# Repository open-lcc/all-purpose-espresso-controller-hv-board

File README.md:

# All-Purpose Espresso Controller HV Board

*Note: The HV does stand for high voltage. It's not high voltage in the technical (>1000 V) sense, but compared to the 12 V in the regular All-Purpose Espresso Controller board, 100-240 VAC is high*

This board is a companion board to the [All Purpose Espresso Controller](https://github.com/open-lcc/all-purpose-espresso-controller) board. Its purpose is to handle some common 100-240 VAC tasks, specifically it has a 12V PSU and four relays.

## Project status

The current hardware revision is R0B. That revision hasn't been manufactured yet, and while this board is pretty simple, and doesn't have any SMD soldering, you probably shouldn't be the first one to manufacture it.

## Disclaimer

Anything you do with this, you do at your own risk. This hardware hasn't even been manufactured by it's creator yet. Your machine uses both line voltage power, high pressured hot water, steam and other dangerous components. You *really* shouldn't be using this yet; in fact, you shouldn't even consider it. Risks include but are not limited to, damaging your machine, personal injury, property damage and summoning dead Cthulhu from his sleep at R'lyeh.

Also, the very purpose of this board is to do things with line voltage. The risk of injury or damage is very real.

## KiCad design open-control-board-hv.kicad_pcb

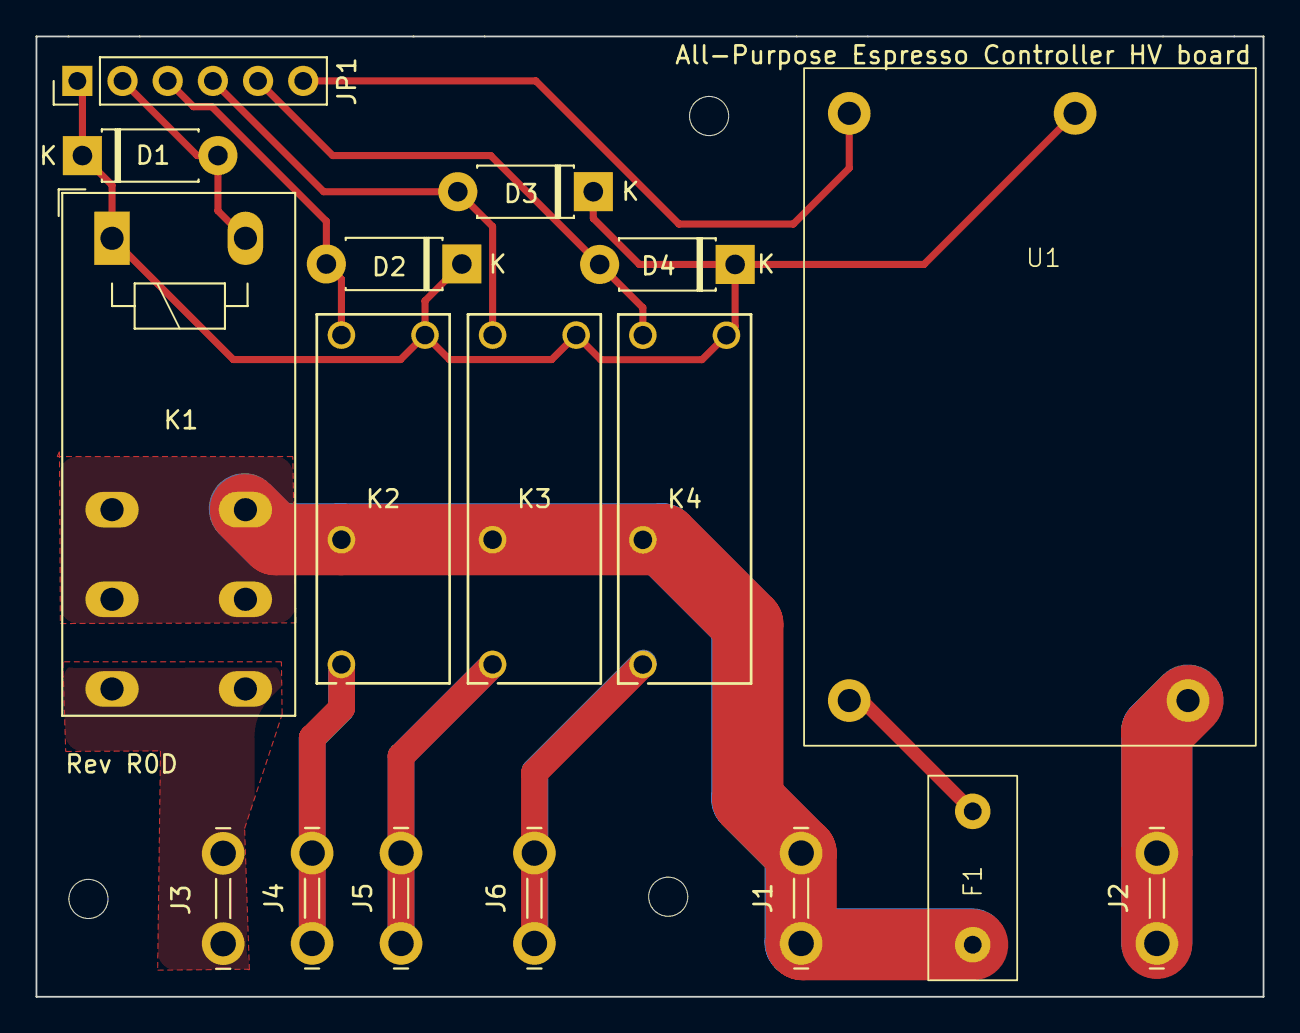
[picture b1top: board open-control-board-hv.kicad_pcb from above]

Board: 2 copper layers, 69.0 x 54.0 mm, 20 parts (0 on the bottom side), 13 nets.

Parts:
D1, D2, D3, D4: 1N4001; D_DO-41_SOD81_P7.62mm_Horizontal
F1: Schurter FRT 250T 7100.1009.13; FRT 250T
H1, H2, H3: MountingHole; MountingHole_2.2mm_M2
J1, J2, J3, J4, J5, J6: TE 160650-2; TE_62409-1
JP1: Conn_01x06_Pin; PinHeader_1x06_P2.54mm_Vertical
K1: RT314A12; Relay_SPDT_Schrack-RT1-16A-FormC_RM5mm
K2, K3, K4: ALDP112; PAN_ALD_PAN
U1: ECE10

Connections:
+12VA: D1.1 (K), D2.1 (K), D3.1 (K), D4.1 (K), JP1.1, K1.A1, K2.4, K3.4, K4.4, U1.4 (+Vout)
FA7_CTRL: D4.2 (A), JP1.5, K4.3
FA8_CTRL: D3.2 (A), JP1.4, K3.3
FA9_CTRL: D2.2 (A), JP1.3, K2.3
FA10_CTRL: D1.2 (A), JP1.2, K1.A2
GND1: JP1.6, U1.3 (-Vout)
N: J2.1, U1.1 (ACN)
unnamed: J3.1, K1.14
unnamed: J4.1, K2.1
unnamed: J5.1, K3.1
unnamed: J6.1, K4.1
PH: F1.1, J1.1, K1.11, K1.12, K2.2, K3.2, K4.2
PH_FUSED: F1.2, U1.2 (ACL)

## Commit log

2024-03-20 Initial import (R0B)
2024-03-24 Updated with manufacturing data and switched footprint for fastons
2024-03-24 Add README and License
2024-03-24 Cleanup
2024-03-29 Added preliminary Gerber for manufacturing
